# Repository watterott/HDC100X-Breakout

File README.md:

# HDC100X-Breakout
Breakout with TI HDC1000 or HDC1008 Digital Humidity and Temperature Sensor.

* [TI HDC1000 or HDC1008](https://www.ti.com/product/hdc1008) Digital Humidity and Temperature Sensor
* Relative Humidity (RH) operating range: 0% to 100%
* Relative Humidity accuracy: HDC1008 +/-4%, HDC1000 +/-3%
* Temperature accuracy: +/-0.2°C
* TWI/I2C Interface (address: 0x43 with ADR0=1 and ADR1=1)
* 3.3V - 5V Power Supply and Logic Level
* Open-Source and released under the [Creative Commons Attribution Share-Alike License](https://creativecommons.org/licenses/by-sa/4.0/).
* **[Documentation on learn.watterott.com](https://learn.watterott.com)**

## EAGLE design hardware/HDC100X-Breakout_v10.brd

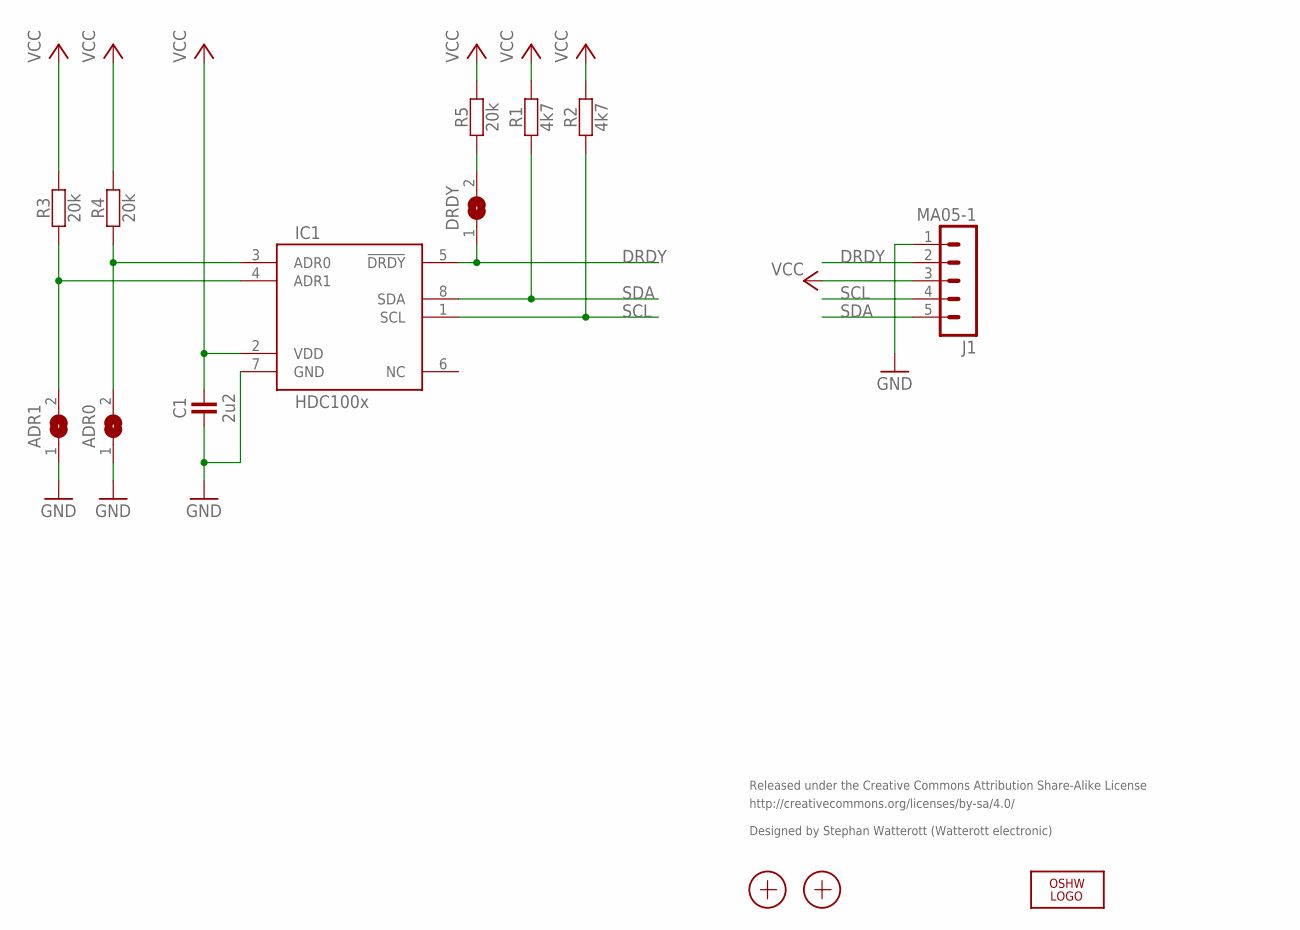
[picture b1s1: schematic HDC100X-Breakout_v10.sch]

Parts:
ADR0, ADR1: JUMPER2-0402
C1: 2u2; R0402
DRDY: JUMPER2-0402
IC1: HDC100x; WLCSP
J1: MA05-1
LOGO2: OSHW_LOGOX0070; OSHW_6X70
R1, R2: 4k7; R0402
R3, R4, R5: 20k; R0402
X1, X2: PASSER-07; PASSER_07MM

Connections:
ADR0: ADR0.2, IC1.3 (ADR0), R4.1
ADR1: ADR1.2, IC1.4 (ADR1), R3.1
DRDY: DRDY.1, IC1.5 (!DRDY), J1.2
GND: ADR0.1, ADR1.1, C1.1, IC1.7 (GND), J1.1
unnamed: DRDY.2, R5.1
SCL: IC1.1 (SCL), J1.4, R2.1
SDA: IC1.8 (SDA), J1.5, R1.1
VCC: C1.2, IC1.2 (VDD), J1.3, R1.2, R2.2, R3.2, R4.2, R5.2

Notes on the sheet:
Released under the Creative Commons Attribution Share-Alike License
http://creativecommons.org/licenses/by-sa/4.0/
Designed by Stephan Watterott (Watterott electronic)

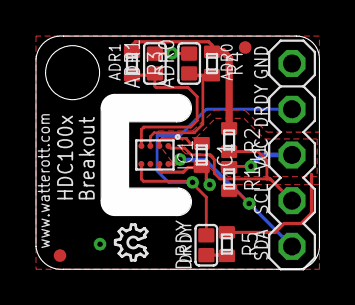
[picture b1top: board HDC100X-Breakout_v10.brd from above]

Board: 2 copper layers, 14.2 x 11.5 mm, 14 parts (0 on the bottom side), 8 nets.

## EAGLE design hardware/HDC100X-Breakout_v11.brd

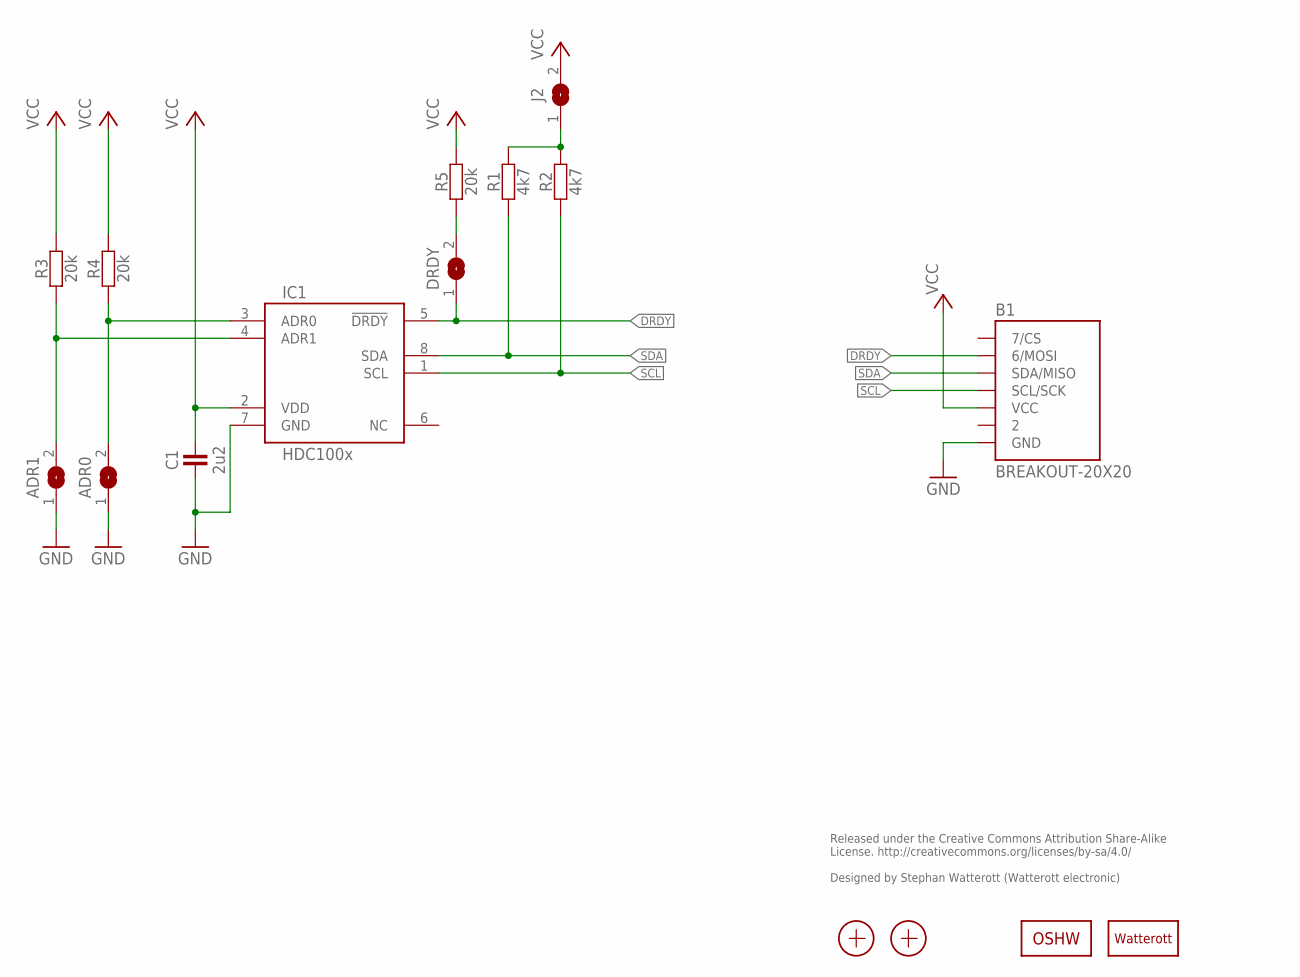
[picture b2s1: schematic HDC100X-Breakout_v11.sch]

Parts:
ADR0, ADR1: JUMPER2-0402
B1: BREAKOUT-20X20
C1: 2u2; R0402
DRDY: JUMPER2-0402
IC1: HDC100x; WLCSP
J2: JUMPER2-0603
LOGO2: OSHW_LOGOX0070; OSHW_6X70
LOGO3: LOGO-S_PLACE_M; SPARK_TPLACE_M
R1, R2: 4k7; R0402
R3, R4, R5: 20k; R0402
X1, X2: PASSER-07; PASSER_07MM

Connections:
ADR0: ADR0.2, IC1.3 (ADR0), R4.1
ADR1: ADR1.2, IC1.4 (ADR1), R3.1
DRDY: B1.MOSI (6/MOSI), DRDY.1, IC1.5 (!DRDY)
GND: ADR0.1, ADR1.1, B1.GND, C1.1, IC1.7 (GND)
unnamed: J2.1, R1.2, R2.2
unnamed: DRDY.2, R5.1
SCL: B1.SCL/SCK, IC1.1 (SCL), R2.1
SDA: B1.SDA/MISO, IC1.8 (SDA), R1.1
VCC: B1.VCC, C1.2, IC1.2 (VDD), J2.2, R3.2, R4.2, R5.2

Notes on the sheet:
Released under the Creative Commons Attribution Share-Alike License. http://creativecommons.org/licenses/by-sa/4.0/ Designed by Stephan Watterott (Watterott electronic)

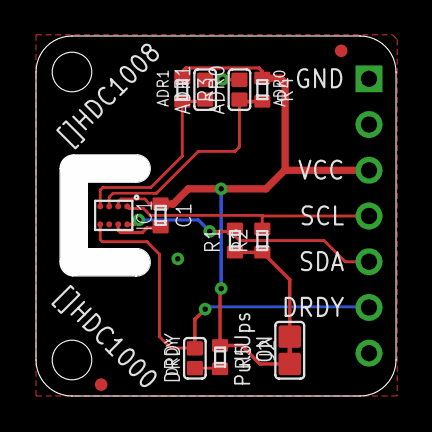
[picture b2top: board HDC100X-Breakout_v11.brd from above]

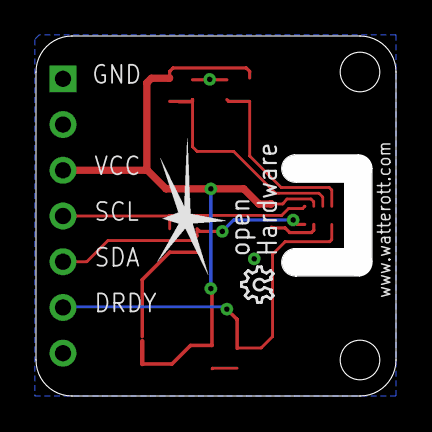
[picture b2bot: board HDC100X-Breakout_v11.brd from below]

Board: 2 copper layers, 18.5 x 18.5 mm, 16 parts (2 on the bottom side), 9 nets.

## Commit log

2015-03-03 added readme
2015-03-03 added layout and schematics
2015-04-18 updated readme and added image
2015-06-27 updated license infos
2015-07-28 updated layout and schematics
2015-08-18 Added link to Windows 10 IoT Library and Examples
